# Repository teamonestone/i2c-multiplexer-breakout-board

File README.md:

# i2c-multiplexer-breakout-board
A Breakout Borad for the Adafruit TCA9548A I²C Multiplexer Board.

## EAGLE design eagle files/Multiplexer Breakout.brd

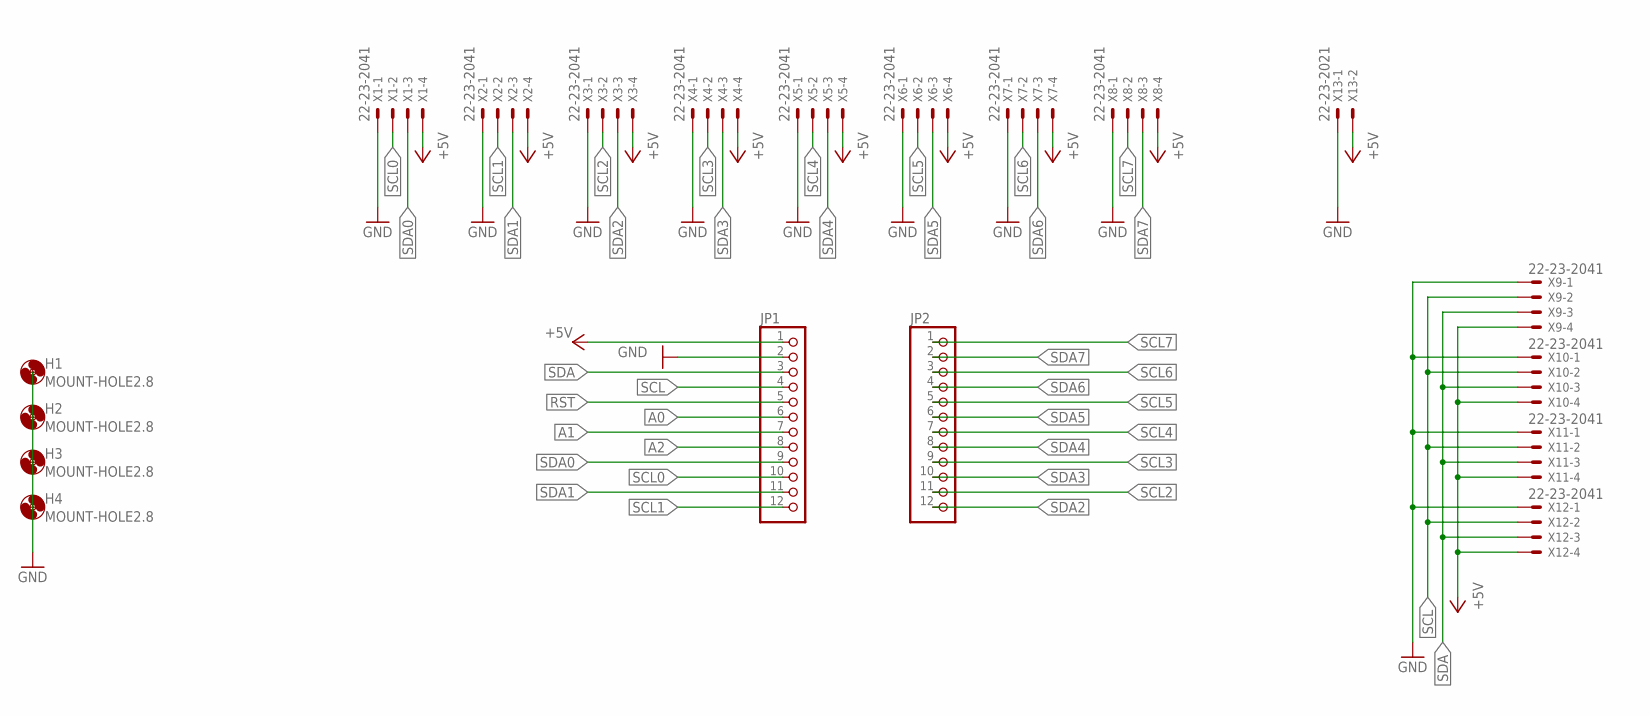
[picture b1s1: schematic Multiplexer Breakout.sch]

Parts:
H1, H2, H3, H4: MOUNT-HOLE2.8; 2,8
JP1, JP2: PINHD-1X12; 1X12
X1, X2, X3, X4, X5, X6, X7, X8, X9, X10, X11, X12: 22-23-2041
X13: 22-23-2021

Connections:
+5V: JP1.1, X1.4, X2.4, X3.4, X4.4, X5.4, X6.4, X7.4, X8.4, X9.4, X10.4, X11.4, X12.4, X13.2
A0: JP1.6
A1: JP1.7
A2: JP1.8
GND: JP1.2, X1.1, X2.1, X3.1, X4.1, X5.1, X6.1, X7.1, X8.1, X9.1, X10.1, X11.1, X12.1, X13.1
RST: JP1.5
SCL: JP1.4, X9.2, X10.2, X11.2, X12.2
SCL0: JP1.10, X1.2
SCL1: JP1.12, X2.2
SCL2: JP2.11, X3.2
SCL3: JP2.9, X4.2
SCL4: JP2.7, X5.2
SCL5: JP2.5, X6.2
SCL6: JP2.3, X7.2
SCL7: JP2.1, X8.2
SDA: JP1.3, X9.3, X10.3, X11.3, X12.3
SDA0: JP1.9, X1.3
SDA1: JP1.11, X2.3
SDA2: JP2.12, X3.3
SDA3: JP2.10, X4.3
SDA4: JP2.8, X5.3
SDA5: JP2.6, X6.3
SDA6: JP2.4, X7.3
SDA7: JP2.2, X8.3

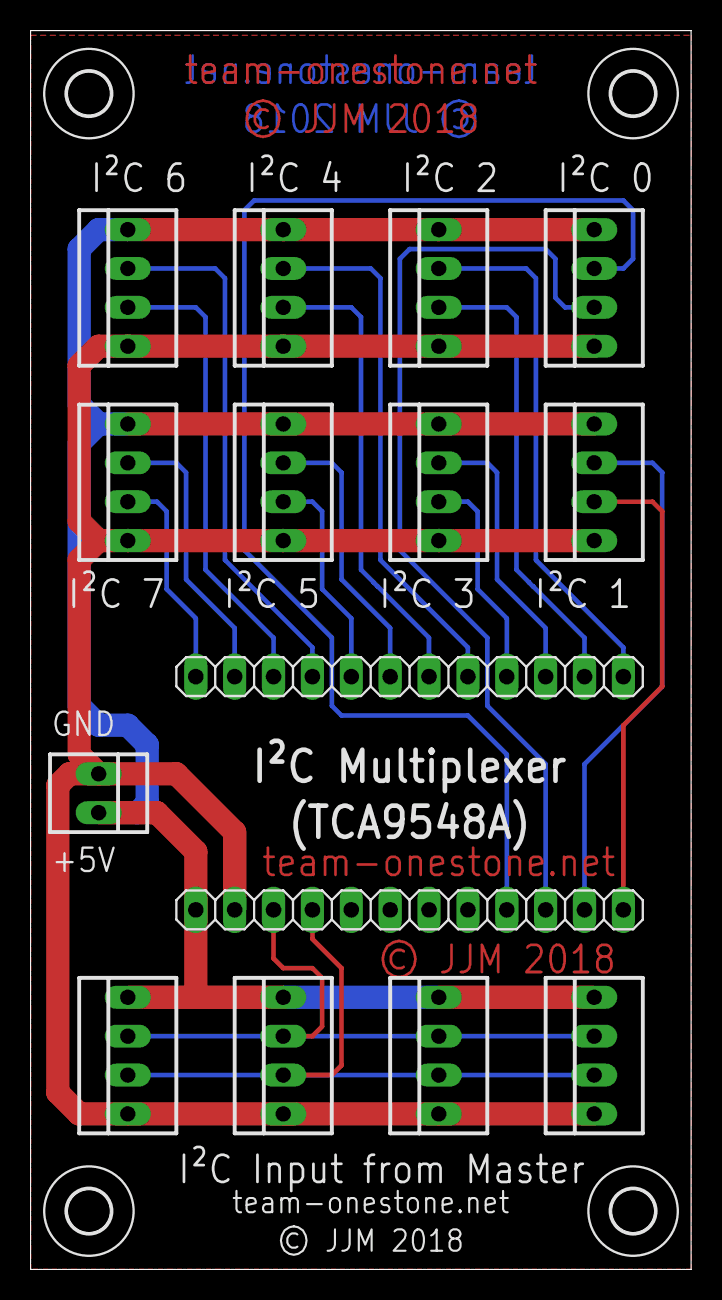
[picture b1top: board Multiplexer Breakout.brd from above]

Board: 2 copper layers, 43.2 x 81.0 mm, 19 parts (0 on the bottom side), 20 nets.

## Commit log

2018-10-21 Create LICENSE
2018-10-21 new gerber & drill data
2018-10-21 eagle bs
2018-10-21 gerber files & co. of first pcb order
2018-11-01 gerber und co neu generiert
2018-11-22 Auf kleinere Stecker umgebaut
2018-11-26 prod version

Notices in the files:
eagle files/Multiplexer Breakout.brd:
© JJM 2018
